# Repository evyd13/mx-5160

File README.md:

# mx-5160
 PCB and plate files for retrofitting MX type switches in a Chicony 5160c

## Whatever you do with these files, I'm not responsible for your mistakes.

Also, the plate for the acrylic case is ISO, please modify for your own use.

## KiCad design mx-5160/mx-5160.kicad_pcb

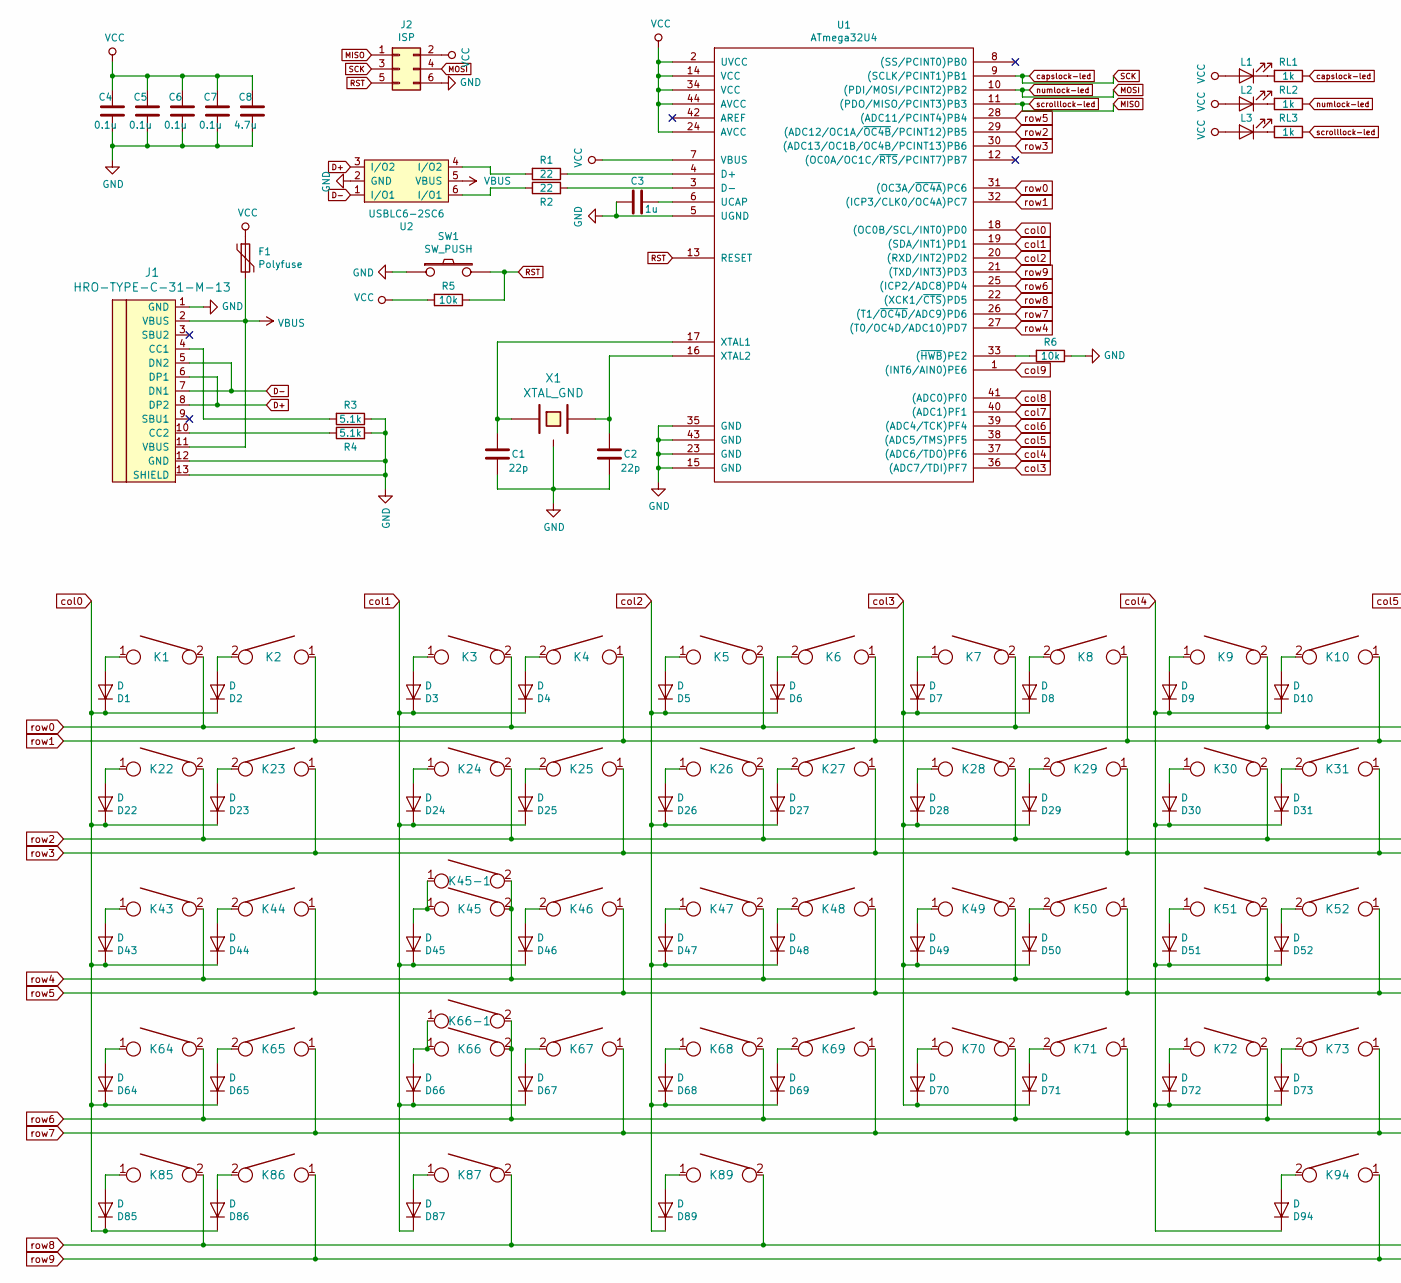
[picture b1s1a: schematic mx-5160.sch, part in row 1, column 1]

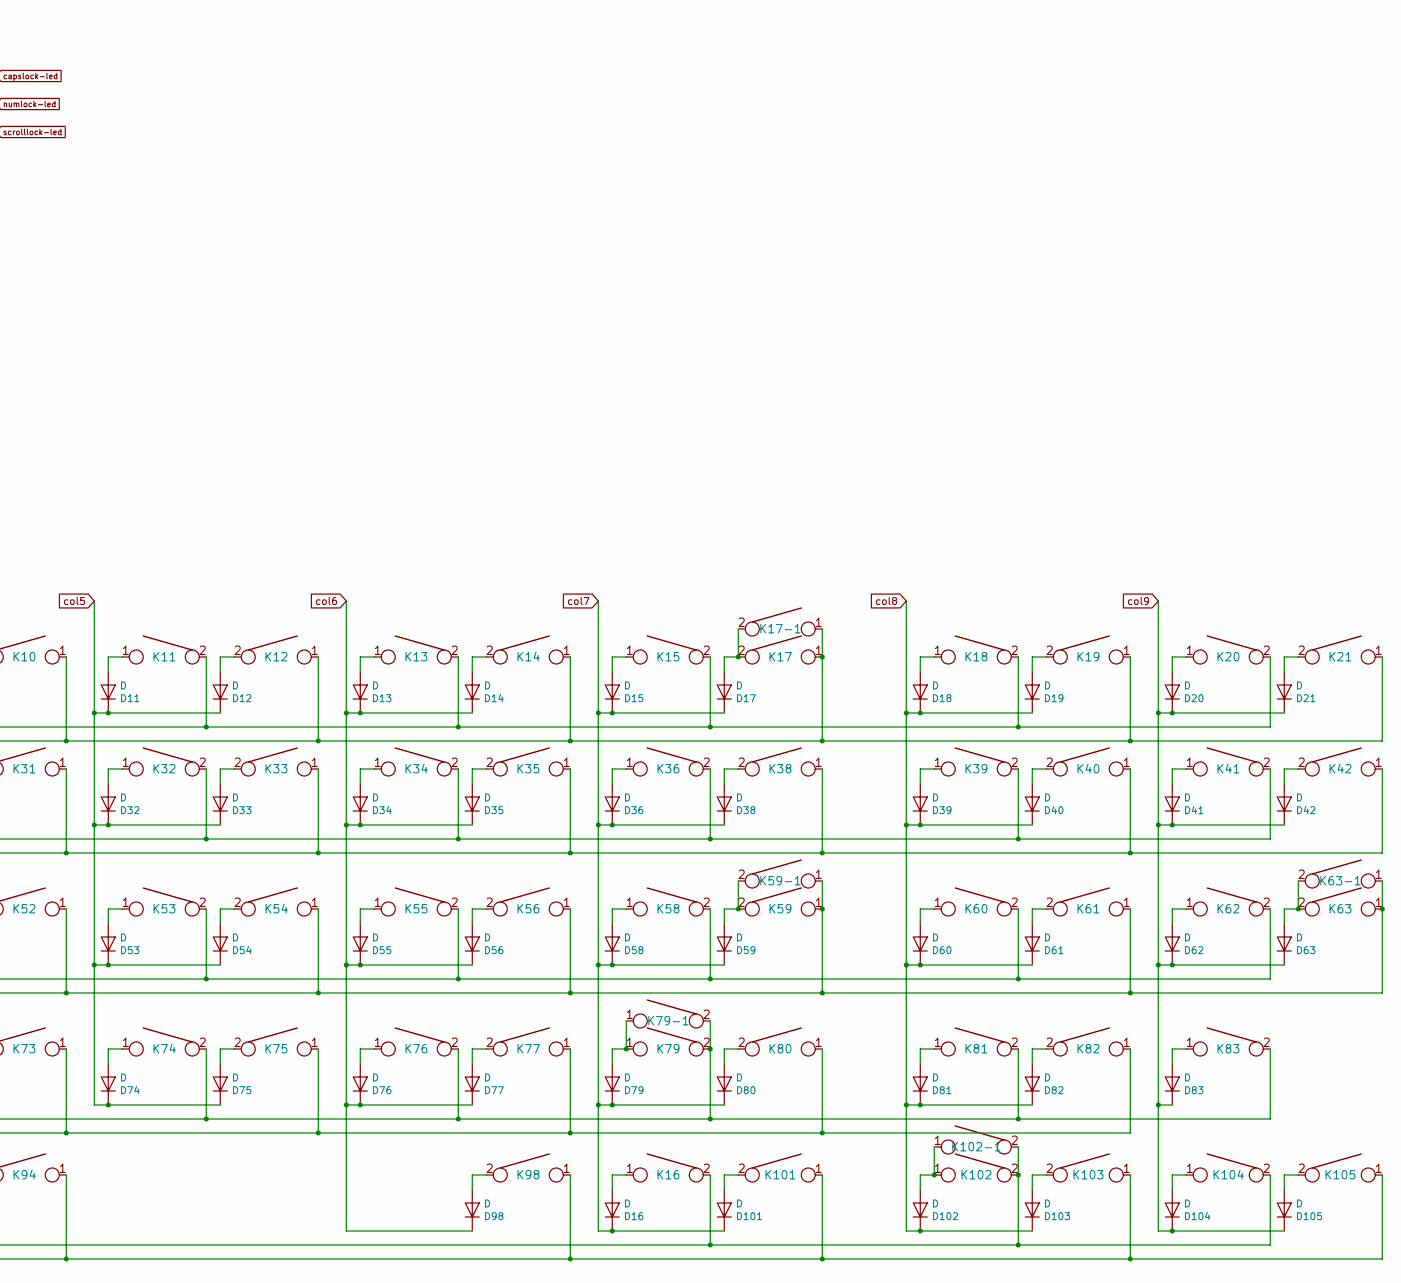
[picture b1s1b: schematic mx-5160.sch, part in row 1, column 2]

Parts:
C1, C2: 22p; C_0805
C3: 1u; C_0805
C4, C5, C6, C7: 0.1u; C_0805
C8: 4.7u; C_0805
D1, D2, D3, D4, D5, D6, D7, D8, D9, D10, D11, D12, D13, D14, D15, D16, D17, D18, D19, D20, D21, D22, D23, D24, D25, D26, D27, D28, D29, D30, D31, D32, D33, D34, D35, D36, D38, D39, D40, D41, D42, D43, D44, D45, D46, D47, D48, D49, D50, D51, D52, D53, D54, D55, D56, D58, D59, D60, D61, D62, D63, D64, D65, D66, D67, D68, D69, D70, D71, D72, D73, D74, D75, D76, D77, D79, D80, D81, D82, D83, D85, D86, D87, D89, D94, D98, D101, D102, D103, D104, D105: D; hybrid_DIODE_sans
F1: Polyfuse; R_0805
J1: HRO-TYPE-C-31-M-13
J2: ISP; isp_standard
K1, K2, K3, K4, K5, K6, K7, K8, K9, K10, K11, K12, K13, K14, K15, K16, K17-1, K18, K19, K20, K21, K22, K23, K25, K26, K27, K28, K29, K30, K31, K32, K33, K34, K35, K36, K39, K40, K41, K42, K43, K44, K46, K47, K48, K49, K50, K51, K52, K53, K54, K55, K56, K58, K60, K61, K62, K63-1, K64, K65, K67, K68, K69, K70, K71, K72, K73, K74, K75, K76, K77, K80, K81, K82, K83, K85, K86, K102-1, K103, K104: KEYSW; CHERRY_PLATE_100H
K17: KEYSW; CHERRY_PCB_200H
K24, K38, K87, K89, K98, K101: KEYSW; CHERRY_PLATE_150H
K45, K79-1: KEYSW; CHERRY_PLATE_175H
K45-1, K66-1: KEYSW; CHERRY_PLATE_125H
K59, K66: KEYSW; CHERRY_PCB_225H
K59-1, K63, K105: KEYSW; CHERRY_PCB_200H_V
K79: KEYSW; CHERRY_PCB_275H
K94: KEYSW; CHERRY_PCB_700H_F
K102: KEYSW; CHERRY_PCB_200H_F
L1, L2, L3: LED; LED_D3.0mm
R1, R2: 22; R_0805
R3, R4: 5.1k; R_0805
R5, R6: 10k; R_0805
RL1, RL2, RL3: 1k; R_0805
SW1: SW_PUSH; SW_SPST_TL3342
U1: ATmega32U4; ATMEGA32U4
U2: USBLC6-2SC6; Farnell 1295310
X1: XTAL_GND; crystal_FA238-TSX3225

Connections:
D+: J1.6 (DP1), J1.8 (DP2), U2.3 (I/O2)
D-: J1.5 (DN2), J1.7 (DN1), U2.1 (I/O1)
GND: C1.1, C2.1, C3.2, C4.1, C5.1, C6.1, C7.1, C8.1, J1.1 (GND), J1.12 (GND), J1.13 (SHIELD), J2.6, R3.1, R4.2, R6.1, SW1.1, U1.5 (UGND), U1.15 (GND), U1.23 (GND), U1.35 (GND), U1.43 (GND), U2.2 (GND), X1.3
MISO: J2.1, RL3.1, U1.11 ((PDO/MISO/PCINT3)PB3)
MOSI: J2.4, RL2.1, U1.10 ((PDI/MOSI/PCINT2)PB2)
unnamed: C1.2, U1.17 (XTAL1), X1.1
unnamed: C2.2, U1.16 (XTAL2), X1.2
unnamed: C3.1, U1.6 (UCAP)
unnamed: D1.2 (A), K1.1
unnamed: D2.2 (A), K2.2
unnamed: D3.2 (A), K3.1
unnamed: D4.2 (A), K4.2
unnamed: D5.2 (A), K5.1
unnamed: D6.2 (A), K6.2
unnamed: D7.2 (A), K7.1
unnamed: D8.2 (A), K8.2
unnamed: D9.2 (A), K9.1
unnamed: D10.2 (A), K10.2
unnamed: D11.2 (A), K11.1
unnamed: D12.2 (A), K12.2
unnamed: D13.2 (A), K13.1
unnamed: D14.2 (A), K14.2
unnamed: D15.2 (A), K15.1
unnamed: D16.2 (A), K16.1
unnamed: D17.2 (A), K17.2, K17-1.2
unnamed: D18.2 (A), K18.1
unnamed: D19.2 (A), K19.2
unnamed: D20.2 (A), K20.1
unnamed: D21.2 (A), K21.2
unnamed: D22.2 (A), K22.1
unnamed: D23.2 (A), K23.2
unnamed: D24.2 (A), K24.1
unnamed: D25.2 (A), K25.2
unnamed: D26.2 (A), K26.1
unnamed: D27.2 (A), K27.2
unnamed: D28.2 (A), K28.1
unnamed: D29.2 (A), K29.2
unnamed: D30.2 (A), K30.1
unnamed: D31.2 (A), K31.2
unnamed: D32.2 (A), K32.1
unnamed: D33.2 (A), K33.2
unnamed: D34.2 (A), K34.1
unnamed: D35.2 (A), K35.2
unnamed: D36.2 (A), K36.1
unnamed: D38.2 (A), K38.2
unnamed: D39.2 (A), K39.1
unnamed: D40.2 (A), K40.2
unnamed: D41.2 (A), K41.1
unnamed: D42.2 (A), K42.2
unnamed: D43.2 (A), K43.1
unnamed: D44.2 (A), K44.2
unnamed: D45.2 (A), K45.1, K45-1.1
unnamed: D46.2 (A), K46.2
unnamed: D47.2 (A), K47.1
unnamed: D48.2 (A), K48.2
unnamed: D49.2 (A), K49.1
unnamed: D50.2 (A), K50.2
unnamed: D51.2 (A), K51.1
unnamed: D52.2 (A), K52.2
unnamed: D53.2 (A), K53.1
unnamed: D54.2 (A), K54.2
unnamed: D55.2 (A), K55.1
unnamed: D56.2 (A), K56.2
unnamed: D58.2 (A), K58.1
unnamed: D59.2 (A), K59.2, K59-1.2
unnamed: D60.2 (A), K60.1
unnamed: D61.2 (A), K61.2
unnamed: D62.2 (A), K62.1
unnamed: D63.2 (A), K63.2, K63-1.2
unnamed: D64.2 (A), K64.1
unnamed: D65.2 (A), K65.2
unnamed: D66.2 (A), K66.1, K66-1.1
unnamed: D67.2 (A), K67.2
unnamed: D68.2 (A), K68.1
unnamed: D69.2 (A), K69.2
unnamed: D70.2 (A), K70.1
unnamed: D71.2 (A), K71.2
unnamed: D72.2 (A), K72.1
unnamed: D73.2 (A), K73.2
unnamed: D74.2 (A), K74.1
unnamed: D75.2 (A), K75.2
unnamed: D76.2 (A), K76.1
unnamed: D77.2 (A), K77.2
unnamed: D79.2 (A), K79.1, K79-1.1
unnamed: D80.2 (A), K80.2
unnamed: D81.2 (A), K81.1
unnamed: D82.2 (A), K82.2
unnamed: D83.2 (A), K83.1
unnamed: D85.2 (A), K85.1
unnamed: D86.2 (A), K86.2
unnamed: D87.2 (A), K87.1
unnamed: D89.2 (A), K89.1
unnamed: D94.2 (A), K94.2
unnamed: D98.2 (A), K98.2
unnamed: D101.2 (A), K101.2
unnamed: D102.2 (A), K102.1, K102-1.1
unnamed: D103.2 (A), K103.2
unnamed: D104.2 (A), K104.1
unnamed: D105.2 (A), K105.2
unnamed: J1.4 (CC1), R3.2
unnamed: J1.10 (CC2), R4.1
unnamed: L1.1 (K), RL1.2
unnamed: L2.1 (K), RL2.2
unnamed: L3.1 (K), RL3.2
unnamed: R1.1, U1.4 (D+)
unnamed: R1.2, U2.4 (I/O2)
unnamed: R2.1, U2.6 (I/O1)
unnamed: R2.2, U1.3 (D-)
unnamed: R6.2, U1.33 ((~HWB~)PE2)
RST: J2.5, R5.1, SW1.2, U1.13 (RESET)
SCK: J2.3, RL1.1, U1.9 ((SCLK/PCINT1)PB1)
VBUS: F1.2, J1.2 (VBUS), J1.11 (VBUS), U2.5 (VBUS)
VCC: C4.2, C5.2, C6.2, C7.2, C8.2, F1.1, J2.2, L1.2 (A), L2.2 (A), L3.2 (A), R5.2, U1.2 (UVCC), U1.7 (VBUS), U1.14 (VCC), U1.24 (AVCC), U1.34 (VCC), U1.44 (AVCC)
col0: D1.1 (K), D2.1 (K), D22.1 (K), D23.1 (K), D43.1 (K), D44.1 (K), D64.1 (K), D65.1 (K), D85.1 (K), D86.1 (K), U1.18 ((OC0B/SCL/INT0)PD0)
col1: D3.1 (K), D4.1 (K), D24.1 (K), D25.1 (K), D45.1 (K), D46.1 (K), D66.1 (K), D67.1 (K), D87.1 (K), U1.19 ((SDA/INT1)PD1)
col2: D5.1 (K), D6.1 (K), D26.1 (K), D27.1 (K), D47.1 (K), D48.1 (K), D68.1 (K), D69.1 (K), D89.1 (K), U1.20 ((RXD/INT2)PD2)
col3: D7.1 (K), D8.1 (K), D28.1 (K), D29.1 (K), D49.1 (K), D50.1 (K), D70.1 (K), D71.1 (K), U1.36 ((ADC7/TDI)PF7)
col4: D9.1 (K), D10.1 (K), D30.1 (K), D31.1 (K), D51.1 (K), D52.1 (K), D72.1 (K), D73.1 (K), D94.1 (K), U1.37 ((ADC6/TDO)PF6)
col5: D11.1 (K), D12.1 (K), D32.1 (K), D33.1 (K), D53.1 (K), D54.1 (K), D74.1 (K), D75.1 (K), U1.38 ((ADC5/TMS)PF5)
col6: D13.1 (K), D14.1 (K), D34.1 (K), D35.1 (K), D55.1 (K), D56.1 (K), D76.1 (K), D77.1 (K), D98.1 (K), U1.39 ((ADC4/TCK)PF4)
col7: D15.1 (K), D16.1 (K), D17.1 (K), D36.1 (K), D38.1 (K), D58.1 (K), D59.1 (K), D79.1 (K), D80.1 (K), D101.1 (K), U1.40 ((ADC1)PF1)
col8: D18.1 (K), D19.1 (K), D39.1 (K), D40.1 (K), D60.1 (K), D61.1 (K), D81.1 (K), D82.1 (K), D102.1 (K), D103.1 (K), U1.41 ((ADC0)PF0)
col9: D20.1 (K), D21.1 (K), D41.1 (K), D42.1 (K), D62.1 (K), D63.1 (K), D83.1 (K), D104.1 (K), D105.1 (K), U1.1 ((INT6/AIN0)PE6)
row0: K1.2, K3.2, K5.2, K7.2, K9.2, K11.2, K13.2, K15.2, K18.2, K20.2, U1.31 ((OC3A/~OC4A~)PC6)
row1: K2.1, K4.1, K6.1, K8.1, K10.1, K12.1, K14.1, K17.1, K17-1.1, K19.1, K21.1, U1.32 ((ICP3/CLK0/OC4A)PC7)
row2: K22.2, K24.2, K26.2, K28.2, K30.2, K32.2, K34.2, K36.2, K39.2, K41.2, U1.29 ((ADC12/OC1A/~OC4B~/PCINT12)PB5)
row3: K23.1, K25.1, K27.1, K29.1, K31.1, K33.1, K35.1, K38.1, K40.1, K42.1, U1.30 ((ADC13/OC1B/OC4B/PCINT13)PB6)
row4: K43.2, K45.2, K45-1.2, K47.2, K49.2, K51.2, K53.2, K55.2, K58.2, K60.2, K62.2, U1.27 ((T0/OC4D/ADC10)PD7)
row5: K44.1, K46.1, K48.1, K50.1, K52.1, K54.1, K56.1, K59.1, K59-1.1, K61.1, K63.1, K63-1.1, U1.28 ((ADC11/PCINT4)PB4)
row6: K64.2, K66.2, K66-1.2, K68.2, K70.2, K72.2, K74.2, K76.2, K79.2, K79-1.2, K81.2, K83.2, U1.25 ((ICP2/ADC8)PD4)
row7: K65.1, K67.1, K69.1, K71.1, K73.1, K75.1, K77.1, K80.1, K82.1, U1.26 ((T1/~OC4D~/ADC9)PD6)
row8: K16.2, K85.2, K87.2, K89.2, K102.2, K102-1.2, K104.2, U1.22 ((XCK1/~CTS~)PD5)
row9: K86.1, K94.1, K98.1, K101.1, K103.1, K105.1, U1.21 ((TXD/INT3)PD3)

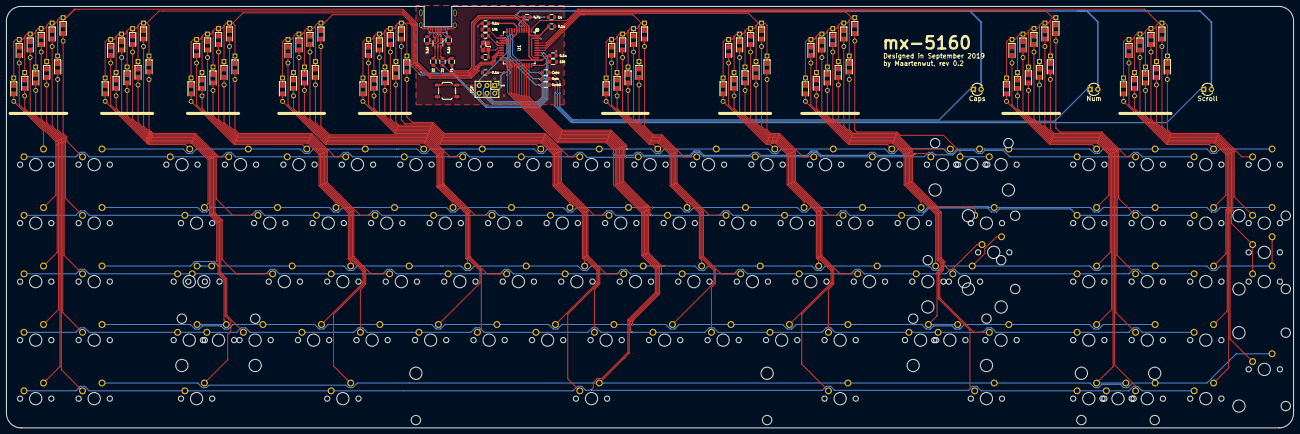
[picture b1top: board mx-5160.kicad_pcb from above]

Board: 2 copper layers, 419.1 x 137.2 mm, 216 parts (0 on the bottom side), 133 nets.

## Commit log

2019-10-19 Upload files of v0.2
2020-03-28 Upload acrylic case
